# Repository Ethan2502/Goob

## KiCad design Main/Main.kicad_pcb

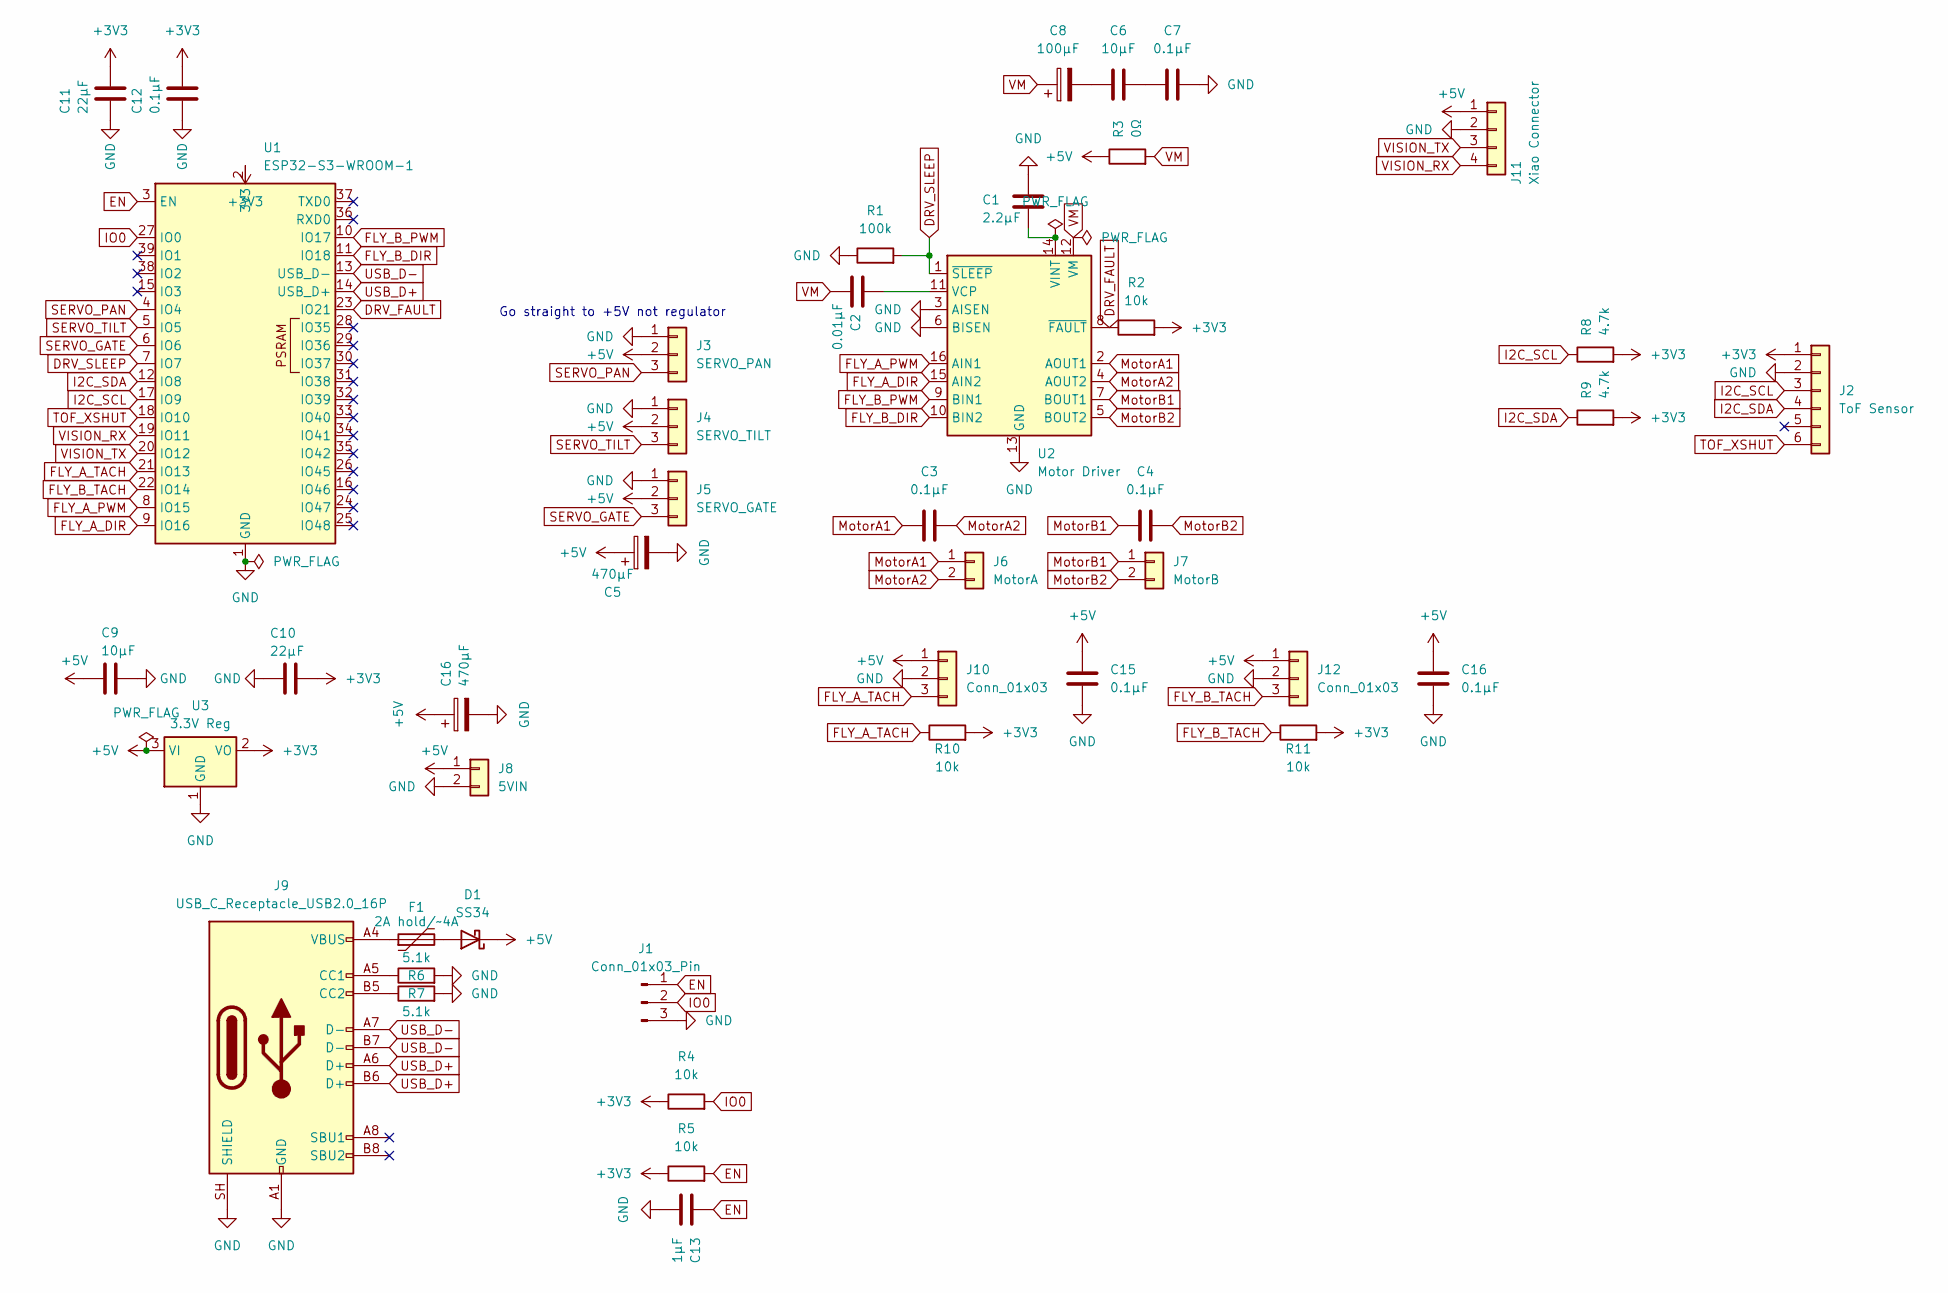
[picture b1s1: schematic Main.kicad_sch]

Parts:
C1: 2.2µF; C_0805_2012Metric
C2: 0.01µF; C_0805_2012Metric
C3, C4, C7, C12, C15: 0.1µF; C_0805_2012Metric
C5: 470µF; CP_Radial_D8.0mm_P3.50mm
C6, C9: 10µF; C_0805_2012Metric
C8: 100µF; C_0805_2012Metric
C10, C11: 22µF; C_0805_2012Metric
C13: 1µF; C_0805_2012Metric
C16: 470µF; CP_Radial_D10.0mm_P5.00mm
D1: SS34; D_SMA
F1: 2A hold/~4A; Fuse_1812_4532Metric
J1: Conn_01x03_Pin; PinHeader_1x03_P2.54mm_Vertical
J2: ToF Sensor; PinHeader_1x06_P2.54mm_Vertical
J3: SERVO_PAN; PinHeader_1x03_P2.54mm_Vertical
J4: SERVO_TILT; PinHeader_1x03_P2.54mm_Vertical
J5: SERVO_GATE; PinHeader_1x03_P2.54mm_Vertical
J6: MotorA; PinHeader_1x02_P2.54mm_Vertical
J7: MotorB; PinHeader_1x02_P2.54mm_Vertical
J8: 5VIN; TerminalBlock_Phoenix_MKDS-1,5-2-5.08_1x02_P5.08mm_Horizont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
J9: USB_C_Receptacle_USB2.0_16P; USB_C_Receptacle_GCT_USB4085
J10, J12: Conn_01x03
J11: Xiao Connector; JST_PH_B4B-PH-K_1x04_P2.00mm_Vertical
R1: 100k; R_0805_2012Metric
R2, R4, R5, R10, R11: 10k; R_0805_2012Metric
R3: 0Ω; R_0805_2012Metric
R6, R7: 5.1k; R_0805_2012Metric
R8, R9: 4.7k; R_0805_2012Metric
U1: ESP32-S3-WROOM-1
U2: Motor Driver; HTSSOP-16-1EP_4.4x5mm_P0.65mm_EP3.4x5mm_Mask2.46x2.31mm_The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
U3: 3.3V Reg; SOT-223-3_TabPin2

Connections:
+3V3: C10.1, C11.1, C12.1, J2.1, R2.2, R4.1, R5.1, R8.2, R9.2, R10.2, R11.2, U1.2 (3V3), U3.2 (VO)
+5V: C5.1, C9.1, C15.1, C16.1, D1.1 (K), J3.2, J4.2, J5.2, J8.1, J10.1, J11.1, J12.1, R3.1, U3.3 (VI); also elsewhere on the board
DRV_FAULT: R2.1, U1.23 (IO21), U2.8 (~FAULT)
DRV_SLEEP: R1.2, U1.7 (IO7), U2.1 (~SLEEP)
EN: C13.1, J1.1, R5.2, U1.3 (EN)
FLY_A_DIR: U1.9 (IO16), U2.15 (AIN2)
FLY_A_PWM: U1.8 (IO15), U2.16 (AIN1)
FLY_A_TACH: J10.3, R10.1, U1.21 (IO13)
FLY_B_DIR: U1.11 (IO18), U2.10 (BIN2)
FLY_B_PWM: U1.10 (IO17), U2.9 (BIN1)
FLY_B_TACH: J12.3, R11.1, U1.22 (IO14)
GND: C1.1, C5.2, C7.2, C9.2, C10.2, C11.2, C12.2, C13.2, C15.2, C16.2, J1.3, J2.2, J3.1, J4.1, J5.1, J8.2, J9.A1 (GND), J9.A12 (GND), J9.B1 (GND), J9.B12 (GND), J9.SH (SHIELD), J10.2, J11.2, J12.2, R1.1, R6.2, R7.2, U1.1 (GND), U1.40 (GND), U1.41 (GND), U2.3 (AISEN), U2.6 (BISEN), U2.13 (GND), U2.17 (GND), U3.1 (GND); also elsewhere on the board
I2C_SCL: J2.3, R8.1, U1.17 (IO9)
I2C_SDA: J2.4, R9.1, U1.12 (IO8)
IO0: J1.2, R4.2, U1.27 (IO0)
MotorA1: C3.2, J6.1, U2.2 (AOUT1)
MotorA2: C3.1, J6.2, U2.4 (AOUT2)
MotorB1: C4.2, J7.1, U2.7 (BOUT1)
MotorB2: C4.1, J7.2, U2.5 (BOUT2)
unnamed: C6.1, C8.2
unnamed: C6.2, C7.1
unnamed: D1.2 (A), F1.2
unnamed: F1.1, J9.A4 (VBUS), J9.A9 (VBUS), J9.B4 (VBUS), J9.B9 (VBUS)
unnamed: J9.A5 (CC1), R6.1
unnamed: J9.B5 (CC2), R7.1
unnamed: C2.1, U2.11 (VCP)
unnamed: C1.2, U2.14 (VINT)
SERVO_GATE: J5.3, U1.6 (IO6)
SERVO_PAN: J3.3, U1.4 (IO4)
SERVO_TILT: J4.3, U1.5 (IO5)
TOF_XSHUT: J2.6, U1.18 (IO10)
USB_D+: J9.A6 (D+), J9.B6 (D+), U1.14 (USB_D+)
USB_D-: J9.A7 (D-), J9.B7 (D-), U1.13 (USB_D-)
VISION_RX: J11.4, U1.19 (IO11)
VISION_TX: J11.3, U1.20 (IO12)
VM: C2.2, C8.1, R3.2, U2.12 (VM)

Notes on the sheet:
Go straight to +5V not regulator

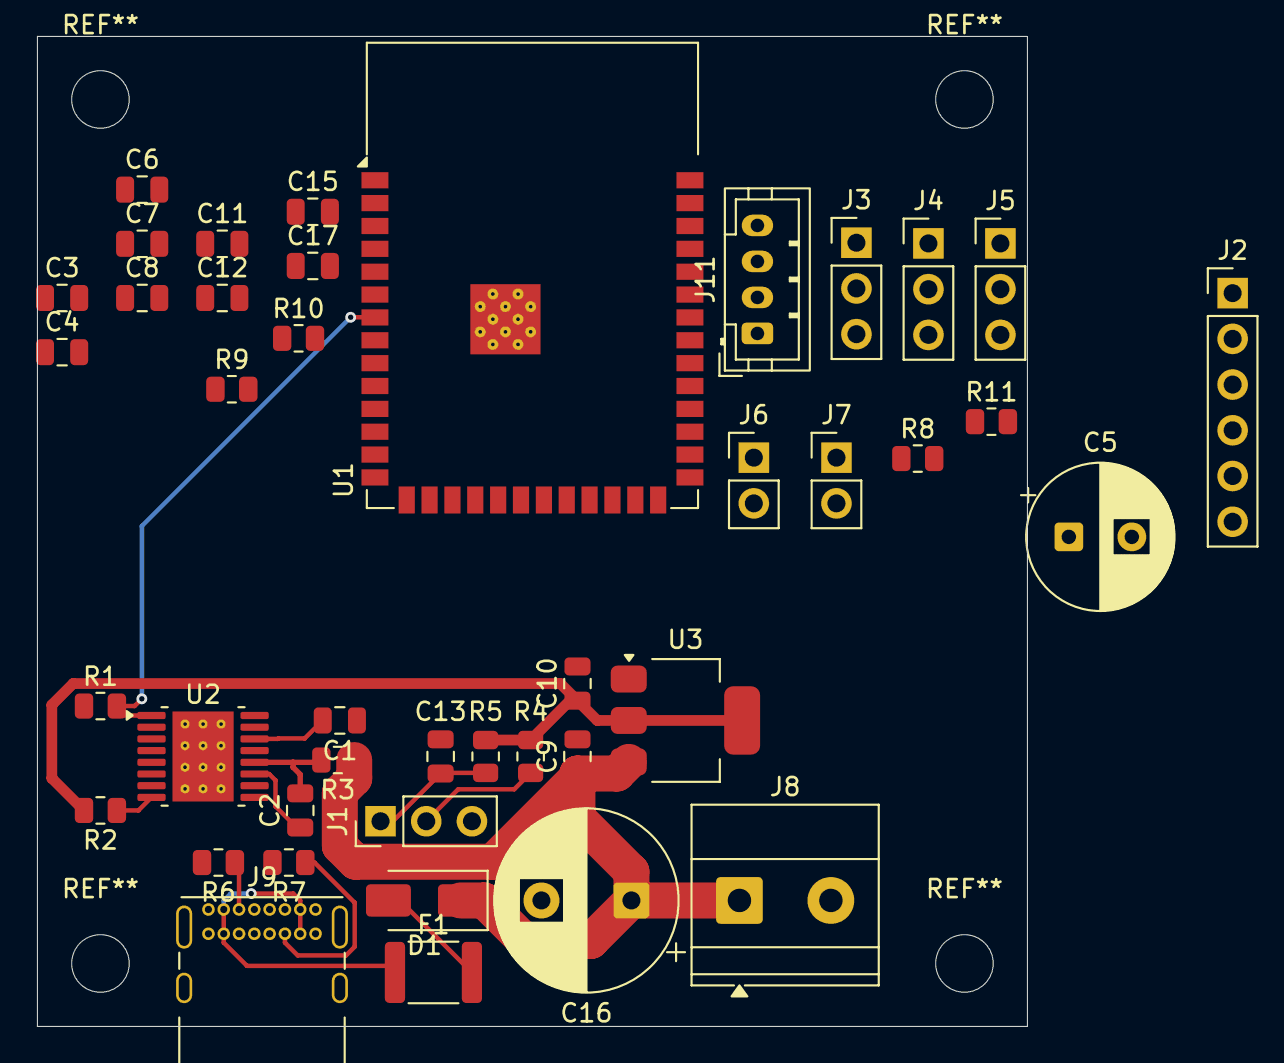
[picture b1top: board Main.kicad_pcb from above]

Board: 2 copper layers, 55.0 x 55.0 mm, 42 parts (0 on the bottom side), 36 nets.

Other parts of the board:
C17: 0.1µF; C_0805_2012Metric

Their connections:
+5V: C17.1; also elsewhere on the board
GND: C17.2; also elsewhere on the board

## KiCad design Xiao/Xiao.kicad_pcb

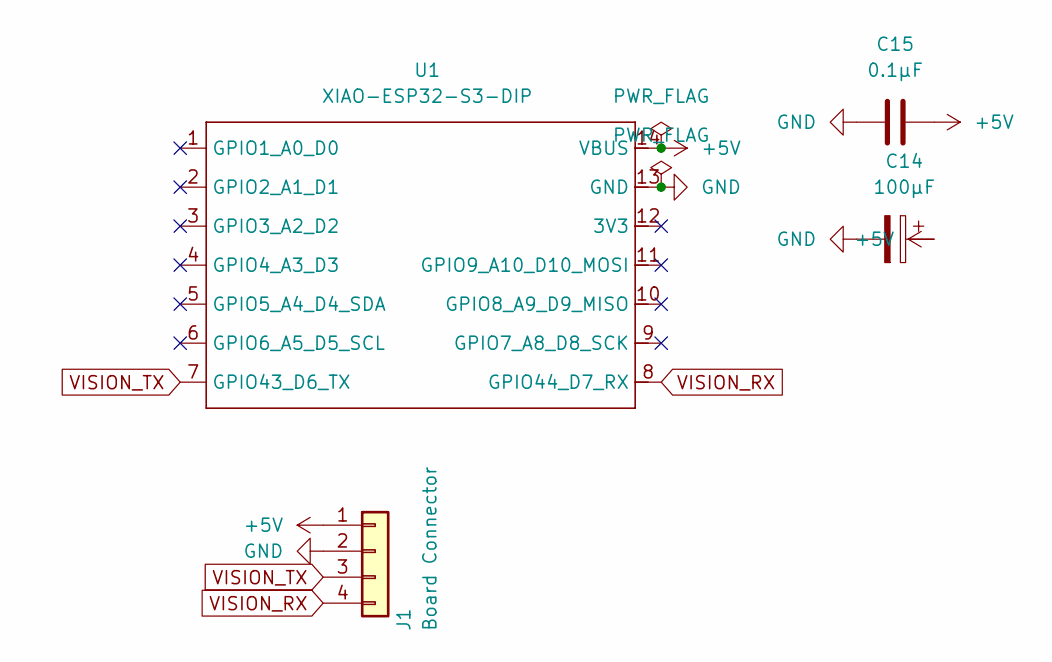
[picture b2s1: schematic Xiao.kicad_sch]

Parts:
C14: 100µF; CP_Elec_6.3x5.4
C15: 0.1µF; C_0805_2012Metric
J1: Board Connector; JST_PH_B4B-PH-K_1x04_P2.00mm_Vertical
U1: XIAO-ESP32-S3-DIP

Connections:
+5V: C14.1, C15.1, J1.1, U1.14 (VBUS)
GND: C14.2, C15.2, J1.2, U1.13 (GND)
VISION_RX: J1.4, U1.8 (GPIO44_D7_RX)
VISION_TX: J1.3, U1.7 (GPIO43_D6_TX)

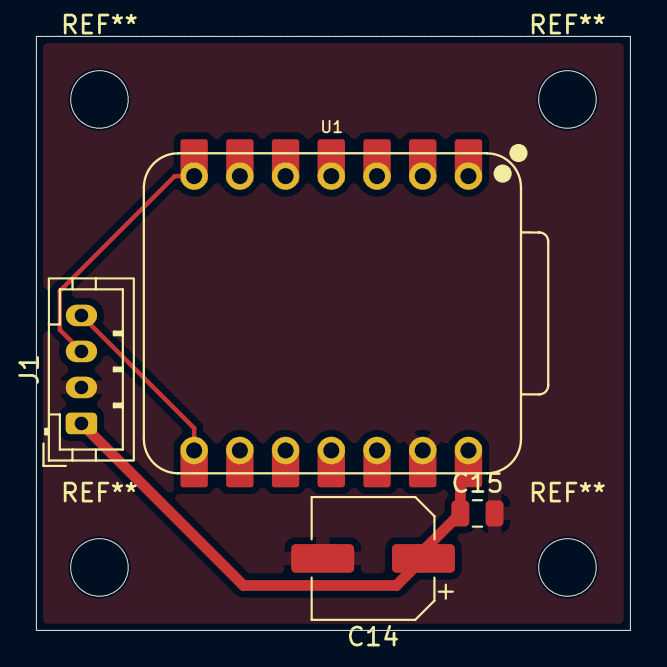
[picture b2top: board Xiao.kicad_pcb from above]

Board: 2 copper layers, 33.0 x 33.0 mm, 4 parts (0 on the bottom side), 4 nets.

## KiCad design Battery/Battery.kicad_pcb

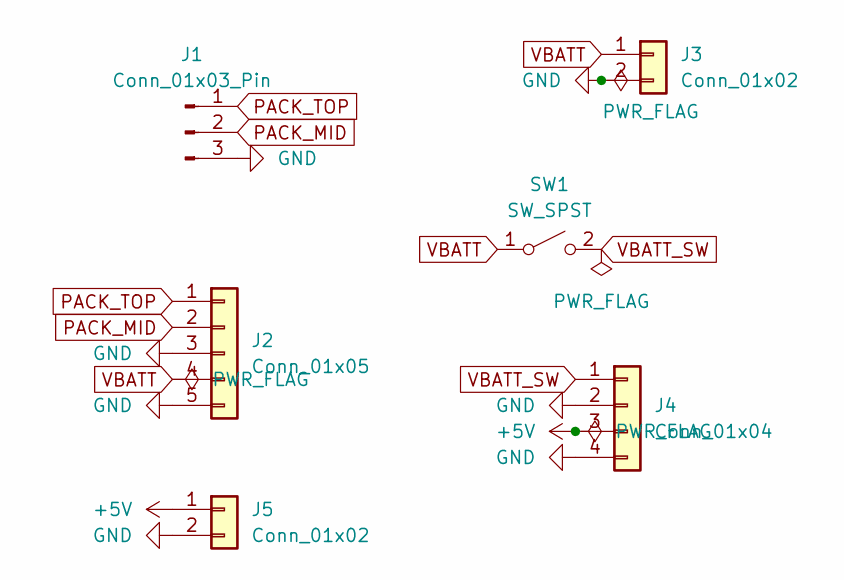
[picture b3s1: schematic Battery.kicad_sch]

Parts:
J1: Conn_01x03_Pin; JST_XH_B3B-XH-A_1x03_P2.50mm_Vertical
J2: Conn_01x05; PinHeader_1x05_P2.54mm_Vertical
J3: Conn_01x02; JST_PH_B2B-PH-K_1x02_P2.00mm_Vertical
J4: Conn_01x04; PinHeader_1x04_P2.54mm_Vertical
J5: Conn_01x02; TerminalBlock_Phoenix_MKDS-1,5-2-5.08_1x02_P5.08mm_Horizont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
SW1: SW_SPST; PinHeader_1x02_P2.54mm_Vertical

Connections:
+5V: J4.3, J5.1
GND: J1.3, J2.3, J2.5, J3.2, J4.2, J4.4, J5.2
PACK_MID: J1.2, J2.2
PACK_TOP: J1.1, J2.1
VBATT: J2.4, J3.1, SW1.1 (A)
VBATT_SW: J4.1, SW1.2 (B)

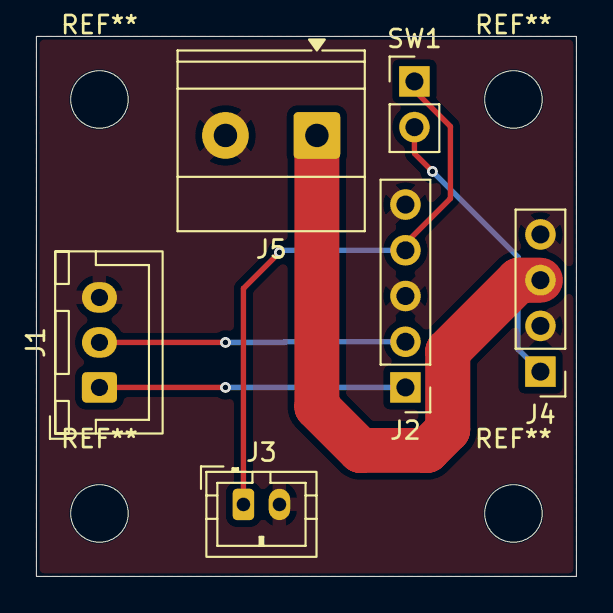
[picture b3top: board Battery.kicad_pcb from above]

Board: 2 copper layers, 30.0 x 30.0 mm, 6 parts (0 on the bottom side), 6 nets.

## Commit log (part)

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2026-06-28 Lots of schematic design
2026-06-30 Battery Schematic and other stuff. Renaming main board files
